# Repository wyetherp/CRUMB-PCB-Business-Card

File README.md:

# CRUMB — PCB Business Card

**Make technology yours.**

This repository contains a guide and the design and manufacturing files to help you make your own printed circuit board (PCB) business card. It lights up and shares a website with your phone through NFC — without a battery.

| Front | Reverse |
| :---: | :---: |
|  |  |

[**Meet the maker and explore CRUMB →**](https://buildcrumb.com/card)

**Before you start:** I'll be honest — this isn't an easy project. This is my second iteration of the card. The first one worked, but not quite the way I wanted it to. All in all, I've probably spent 70–100 hours on this project.

There are a lot of finicky steps along the way, but with enough time, patience and a willingness to figure things out, you can make one yourself. Think of this guide as a journal of my experience rather than a complete, step-by-step tutorial. I've tried to document as much as I can, including the files I used and the lessons I learned, but I can't cover every little detail or edge case you might encounter.

If you get stuck or have any questions, feel free to reach out to me at [wyeth@buildcrumb.com](mailto:wyeth@buildcrumb.com). I'm happy to help.

## How the card works

The gold antenna is more than decoration. Bring a compatible NFC-enabled phone close to the card and its short-range electromagnetic field couples with the antenna. The NFC chip can use energy from that field, and the card's circuitry can illuminate its LED. The phone reads the stored web address and offers to open it. This passive design needs no battery or charging.

**Try it:** unlock your phone and bring its NFC reader close to the antenna. If the notification appears, tap it. If NFC is unavailable or disabled, scan the printed QR code with the camera instead.

This is the operating principle, not a circuit schematic. Exact chip type, antenna tuning, and LED power circuitry still need to be checked against the original design.

## From idea to finished card

I developed the concept and worked with a [PCB designer on Fiverr](https://www.fiverr.com/s/VrDaVdY) on the electrical design. He helped turn the idea into a circuit board. I handled manufacturing preparation, ordering, testing, NFC configuration, and integration with the CRUMB website.

The difficult part was getting the board assembled. I initially had neither the bill of materials (BOM) nor the pick-and-place file (CPL), and had to prepare them before placing the order. I ran into several snags along the way. Receiving a working card made the difference between designing something and actually manufacturing it clear.

You don't have to be an electrical engineer to turn an idea into a product, but this project does require some technical knowledge and patience. I collaborated with a designer, learned the manufacturing process, and tested the result. This is a case study of what I was able to build, not a guaranteed beginner tutorial.

## Make your own PCB business card

Here is the path I took, including the two steps that actually make the finished card usable: ordering it assembled and writing the NFC link.

**What did it cost?**

Around $30 was an option for bare, unassembled boards. But a bare board is not a working NFC card. Unless you have the equipment and experience to hand-solder extremely small surface-mount components, I recommend selecting PCB Assembly (PCBA) and letting the manufacturer assemble the circuit for you.

Here is what I actually spent:

- **$250 — PCB design.** I worked with [this PCB designer on Fiverr](https://www.fiverr.com/s/VrDaVdY). He helped bring my idea to life, and I recommend him based on my experience.
- **$250 — 15 assembled boards.** This included manufacturing, component assembly, shipping, taxes and tariffs.

**Total: $500 for 15 cards, or approximately $33.33 per card**, including the initial design cost. The assembled-board order alone worked out to about $16.67 per card. The design is a one-time expense if you reuse it unchanged, so future orders can cost less per card. These are my project's costs, not guaranteed manufacturing quotes.

1. **Get the design and manufacturing files.** Work with a PCB designer or adapt a reviewed design. Obtain the Gerbers and drills, BOM, and pick-and-place file before ordering.
2. **Select PCB Assembly (PCBA).** Ordering a PCB alone gets you a bare board, not a working card. I ordered the boards assembled so the NFC chip, LED and other components arrived soldered in place.
3. **Program the card with NFC Tools.** I used the app on my phone to write the website address onto the NFC chip.
4. **Test it.** Tap the card with a compatible phone, check that the website opens and the LED responds, and scan the printed QR code.

The detailed chapters below explain the general process. Start with the fundamentals if you are new to PCB design; don't place an order until your files and assembly preview have been reviewed.

## Rev 3.0 project files

| File | Purpose |
| --- | --- |
| [Gerber ZIP](CRUMB-PCB-Rev3-Gerbers.zip?raw=true) | Fabrication archive, including drill files |
| [Individual Gerber and drill files](CRUMB%20PCB%20card%20gerbers/) | Inspect the manufacturing layers |
| [BOM (XLS)](bom.xls?raw=true) | Parts list and JLCPCB part numbers |
| [JLCPCB-formatted CPL](CRUMB_Rev3_JLCPCB_CPL_Formatted.csv?raw=true) | Factory-ready placement format |
| [Original KiCad position export](PCB_Business_card_Rev_3.0-all-pos.csv?raw=true) | Original placement reference, not an additional assembly file |
| [KiCad project, board and schematic](source/) | Editable design source |

The BOM and both placement files describe the same four fitted components: C1 (220 nF), R3 (220 Ω), D1 (0402 LED), and U1 (NT3H1101W0FHKH). Use the formatted CPL for the JLCPCB upload, not both placement files. **Assembly is on both sides:** D1 is on the bottom; C1, R3 and U1 are on the top.

The Gerber ZIP contains 12 files, including the two drill files. The individual files match the archive's recorded CRC checksums. The Gerber job metadata describes a two-layer, 1.6 mm board, approximately 86.65 × 54.81 mm; this does not establish the exact successful factory order settings. The actual finish, part availability, assembly selection and pricing must be confirmed before ordering.

The recovered KiCad source has not yet been independently checked by regenerating all manufacturing outputs. It references custom symbol/footprint libraries that are not included as separate library files; check the embedded design and missing-library warnings before editing or regenerating outputs. This is a project case study and general workflow, not a guarantee that a new order will work unchanged.

### Customize an existing design

If you have permission to use an existing, complete design, make a separate copy of its KiCad project. Confirm the license, inspect the actual copper, mask and silkscreen layers, and identify the artwork and QR-code elements. Replace only the intended text and decorative geometry, then validate the new QR destination. Preserve the NFC antenna, routing, pads, component layout and electrical clearances unless a qualified designer reviews the changes. Artwork changes on conductive layers can affect antenna performance.

### Design your own from scratch

Learn PCB design using [KiCad's PCB Editor documentation](https://docs.kicad.org/9.0/en/pcbnew/pcbnew.html), or [work with the designer who helped me](https://www.fiverr.com/s/VrDaVdY). Specify the intended phone interaction, LED behavior, card dimensions, finish and target manufacturer. Request editable schematic and board source, all required custom footprints and artwork, manufacturing outputs, assembly drawing, BOM, pick-and-place data, and design rules. Agree on ownership and redistribution rights in writing.

### 01. Understand the PCB and NFC

A printed circuit board (PCB) holds components and electrically connects them using conductive traces. A passive NFC tag exchanges a small amount of data with a nearby reader and gets operating energy from the reader's field. Start with a known working NFC design; antenna geometry, tuning, component ratings and energy harvesting need engineering review. Decide what your card should communicate and whether it needs a light.

### 02. Obtain and edit the design files

Open the editable KiCad project, not just exported Gerbers. Inspect the schematic and board layout together, check for missing libraries, and confirm the intended manufacturing revision. Identify decorative layers before editing. Check the QR code on a printed proof and update all personal text, URLs and artwork consistently. Run electrical and board design-rule checks and review any warnings with the designer.

### 03. Prepare Gerbers and drill files

Gerbers describe the geometry of the physical board layers: copper, solder mask, silkscreen and outline as applicable. Drill files describe holes. Export the required layers and drills from the PCB editor using your manufacturer's accepted format. Inspect every output in a Gerber viewer for board outline, antenna, text, mask openings, and alignment. Do not assume an export preset matches your factory's requirements.

### 04. Understand the bill of materials (BOM)

The BOM is the parts list: reference designators, quantities, manufacturer part numbers, packages and values. Match it to the exact schematic and board revision. Confirm the assembly service has each part in stock, including the NFC chip and LED. Do not accept a substitution simply because its package looks similar; electrical characteristics and compatibility matter.

### 05. Understand the pick-and-place file

The component placement list (CPL or pick-and-place file) tells the assembly machine where each fitted component belongs, on which side, and with what rotation. Match its reference designators to the BOM and layout. Confirm units, origin, sides, and rotations against the factory's requirements and assembly preview. Pay particular attention to polarized LEDs, IC pin 1, and any parts that should not be placed.

### 06. Order fabricated and assembled boards

**Select PCB Assembly (PCBA)** if you want the manufacturer to install the parts. PCB fabrication alone creates the bare board. PCBA adds the component placement and soldering needed to make the circuit functional.

The bare-board option was around $30, but it would have required hand-soldering extremely small components. I chose PCBA and paid approximately $250 for 15 assembled boards, including shipping, taxes and tariffs. That is about $16.67 per assembled board before the separate $250 design cost. Actual quotes depend on the design, quantity, components and shipping.

Upload the Gerbers and drill files for fabrication, then the BOM and pick-and-place file for assembly. Confirm the component selections, orientation, board finish and dimensions against the reviewed design. Select assembly on both sides for this design; the LED is on the bottom. Use the formatted JLCPCB CPL linked above. Check both previews and the full quote before paying. This is the general ordering workflow, not a verified list of my exact factory settings.

### 07. Inspect and test the delivered boards

Check the board finish, outline, artwork, antenna and component population against the design. Inspect joints and orientations for visible defects; do not apply an external supply to a passive design unless the schematic specifies it. Test NFC reading with a compatible phone, confirm the intended LED response, and test the QR code. Record which boards pass and the conditions used for testing.

### 08. Program an NFC website link

I used **NFC Tools** on my phone to program the website link onto the assembled card. On a compatible phone and writable NFC tag:

1. Install NFC Tools by wakdev and open the Write tab.
2. Choose Add a record, select URL / URI, and enter your full website address. I used `https://buildcrumb.com/card/`.
3. Confirm the record, select Write, and hold the card near the phone's NFC reader until the app confirms success.
4. Read the card again, test the website link, and check the LED and printed QR code.

See the [official NFC Tools URL-writing instructions](https://www.wakdev.com/en/knowledge-base/how-to-guides/how-to-write-a-link-url-on-an-nfc-chip.html) for the app screens. Some tags are read-only or incompatible. Do not permanently lock the tag until you have verified the correct destination and understand that locking may be irreversible.

### 09. Troubleshoot common problems

If no NFC notification appears, check phone compatibility, NFC settings, reader position, metal interference, and whether the tag can be read with a compatible app. If the URL is wrong, read back the stored record and reprogram only if writable. If the LED does not light, compare orientation, component population and antenna/circuit design with the verified assembly; ask the designer to diagnose it. If an order preview shows missing or rotated parts, reconcile the BOM and placement files before approval.

## Further reading

- [KiCad PCB Editor documentation](https://docs.kicad.org/9.0/en/pcbnew/pcbnew.html) — exporting fabrication outputs, drills and placement files.
- [PCB assembly file requirements and ordering example](https://jlcpcb.com/help/article/pcb-assembly-faqs) — a manufacturer's explanation of fabrication files, BOM and placement data.
- [Component matching and file preparation](https://jlcpcb.com/help/article/advice-for-bom-and-cpl-files-preparation) — one manufacturer's format and designator requirements.
- [NFC tags and passive power](https://developer.att.com/technical-library/device-technologies/nfc-tags) — an introduction to NFC data and energy transfer.

## About CRUMB and reuse rights

CRUMB is a free educational workshop for people who want to understand, build and customize technology. This repository is the home of the full manufacturing guide and project files. The [card showcase](https://buildcrumb.com/card/) introduces the project and provides contact information and links to the wider workshop.

The electrical hardware design and manufacturing files (KiCad source, Gerbers, drill files, BOM and placement files) are licensed under the [CERN Open Hardware Licence v2 — Permissive (CERN-OHL-P-2.0)](LICENSE), to the extent CRUMB holds the necessary rights. You may study, modify, manufacture, share and sell your own versions under the licence terms, including retaining applicable notices and documenting modifications when distributing modified source.

CRUMB branding, original artwork, photographs and personal contact information are not included in this hardware licence. Replace these elements with your own before distributing your customized cards. Third-party materials remain subject to their applicable rights. The design is provided as-is, without warranty; verify your manufacturing files before ordering.

Earlier versions distributed under the MIT License retain any rights validly granted under that licence.

**[Explore CRUMB](https://buildcrumb.com/build/) · [Card showcase](https://buildcrumb.com/card/) · [Contact](mailto:wyeth@buildcrumb.com)**

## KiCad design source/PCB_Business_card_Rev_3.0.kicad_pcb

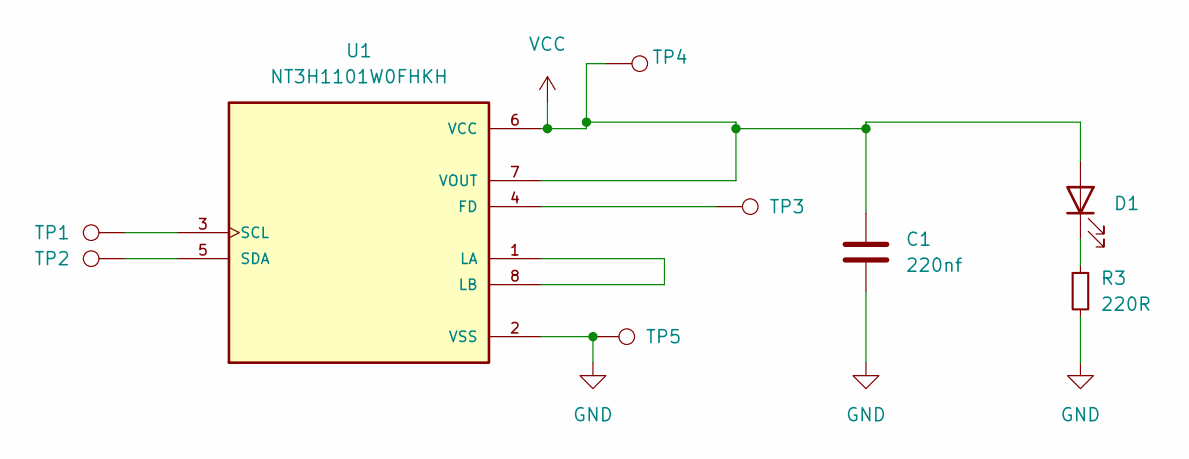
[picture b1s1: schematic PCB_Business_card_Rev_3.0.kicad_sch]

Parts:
C1: 220nf; C_0402_1005Metric
D1: LED; LED_0402_1005Metric
R3: 220R; R_0402_1005Metric
TP1, TP2, TP3, TP4, TP5: TestPoint; TestPoint_Pad_D1.0mm
U1: NT3H1101W0FHKH; IC_NT3H1101W0FHKH; PARTREV 3.3

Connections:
GND: C1.2, R3.2, TP5.1, U1.2 (VSS)
unnamed: D1.1 (K), R3.1
unnamed: TP3.1, U1.4 (FD)
unnamed: U1.1 (LA), U1.8 (LB)
unnamed: TP1.1, U1.3 (SCL)
unnamed: TP2.1, U1.5 (SDA)
VCC: C1.1, D1.2 (A), TP4.1, U1.6 (VCC), U1.7 (VOUT)

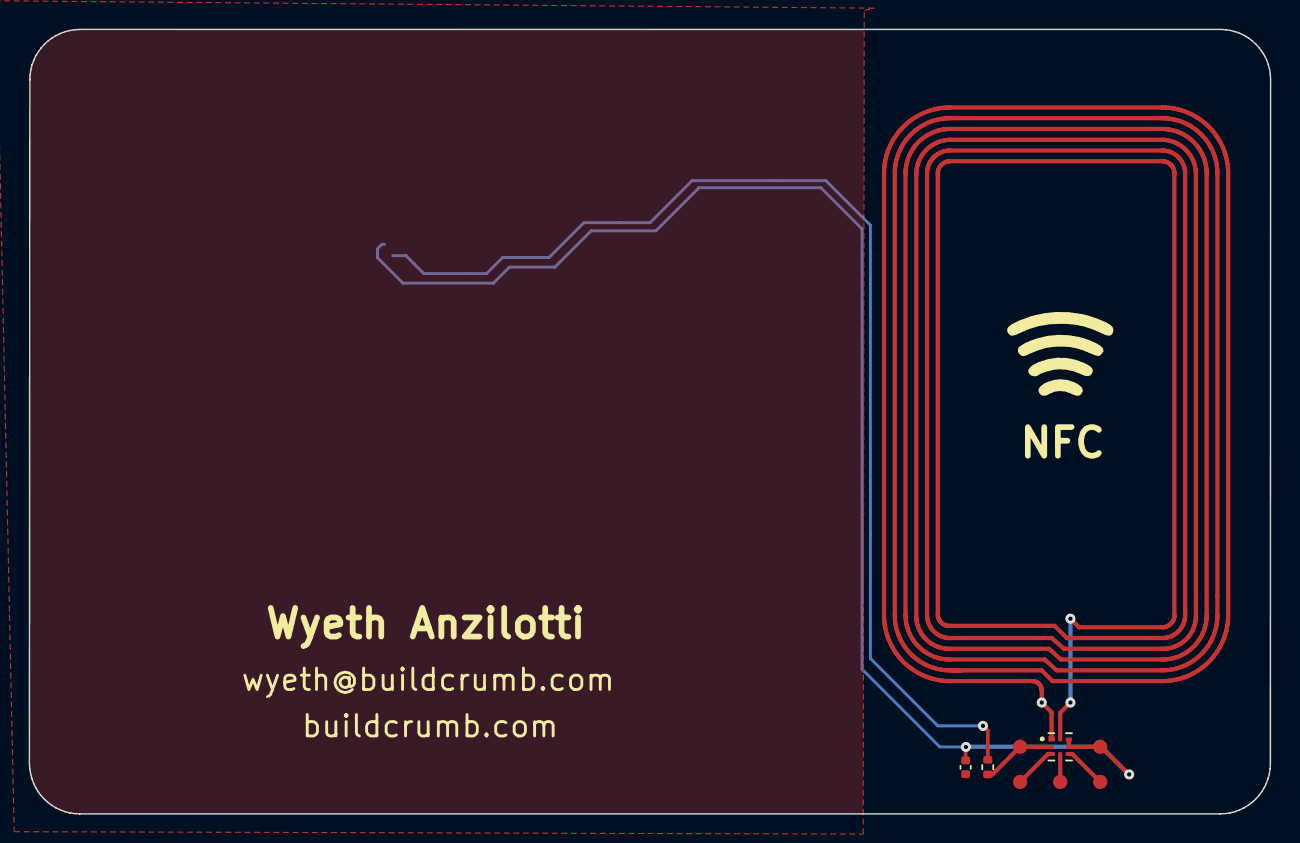
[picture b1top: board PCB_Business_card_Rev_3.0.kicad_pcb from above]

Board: 2 copper layers, 86.6 x 54.7 mm, 9 parts (1 on the bottom side), 7 nets.
